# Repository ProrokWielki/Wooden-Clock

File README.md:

# PROJECT IN PROGRESS #

## How to build ##

### Pull the repo and all submodules ###

```
git clone --recurse-submodules https://github.com/ProrokWielki/Wooden-Clock.git
```

### Pull the docker image ###
```
docker pull pawelwarzecha/wooden_clock:0.5.2
```

### Run docker ###

```
docker run \
  --privileged \
  --network=host \
  -e DISPLAY=:0 \
  -e XAUTHORITY=/tmp/.Xauthority \
  -v $HOME/.Xauthority:/tmp/.Xauthority \
  -v /dev/bus/usb:/dev/bus/usb \
  -v /dev/:/dev/ \
  -v ./Wooden-Clock:/workspaces \
  -it pawelwarzecha/wooden_clock:0.5.2
```

### Build - inside docker ###

#### Supported build types ###
```
    ARM_Release  Release build - no debug symbols and 02
    ARM_Debug    Debug build - debug symbols and 00
    ARM_Size     Size optimized build - no debug symbols
    ARM_Speed    Speed optimized build - no debug symbols
    x86_Clang    Builds libs and unit tests for host machine using clang
    x86_GCC      Builds libs and unit tests for host machine using gcc
```
* **x86_*** builds are used for testing the project on the PC. CAn be used to run unit tests or use the GUI to emulate the hardware.
* **ARM_*** builds are for running the project on the dedicated board and running the `HIL` tests.

#### building ####

```
cd /workspaces/Software/STM
mkdir build
cd build
cmake -DCMAKE_BUILD_TYPE=<BUILD_TYPE> ..
make
```

## Running ##

### x86 build ###

#### Running unit tests ####

```
make test
```

#### Running the simulator ####

```
./src/pc/WoodenClockSimulator
```

### ARM build ###

For this you need to connect the board to the PC to be able to flash the software.

#### Running HIL tests ####

This will flash the target with the test bin and test if the behavior of the board is correct.

```
make test
```

#### Flashing the software ####

##### Flashing the internal flash ####

```
make flash
```

##### Flahsing the external flash ####

```
cd /workspaces/Software/Flasher
make
./flasher.py --file /workspaces/Software/STM/buil2/src/stm32/WoodenClock.elf --dev /dev/ttyUSB0
```

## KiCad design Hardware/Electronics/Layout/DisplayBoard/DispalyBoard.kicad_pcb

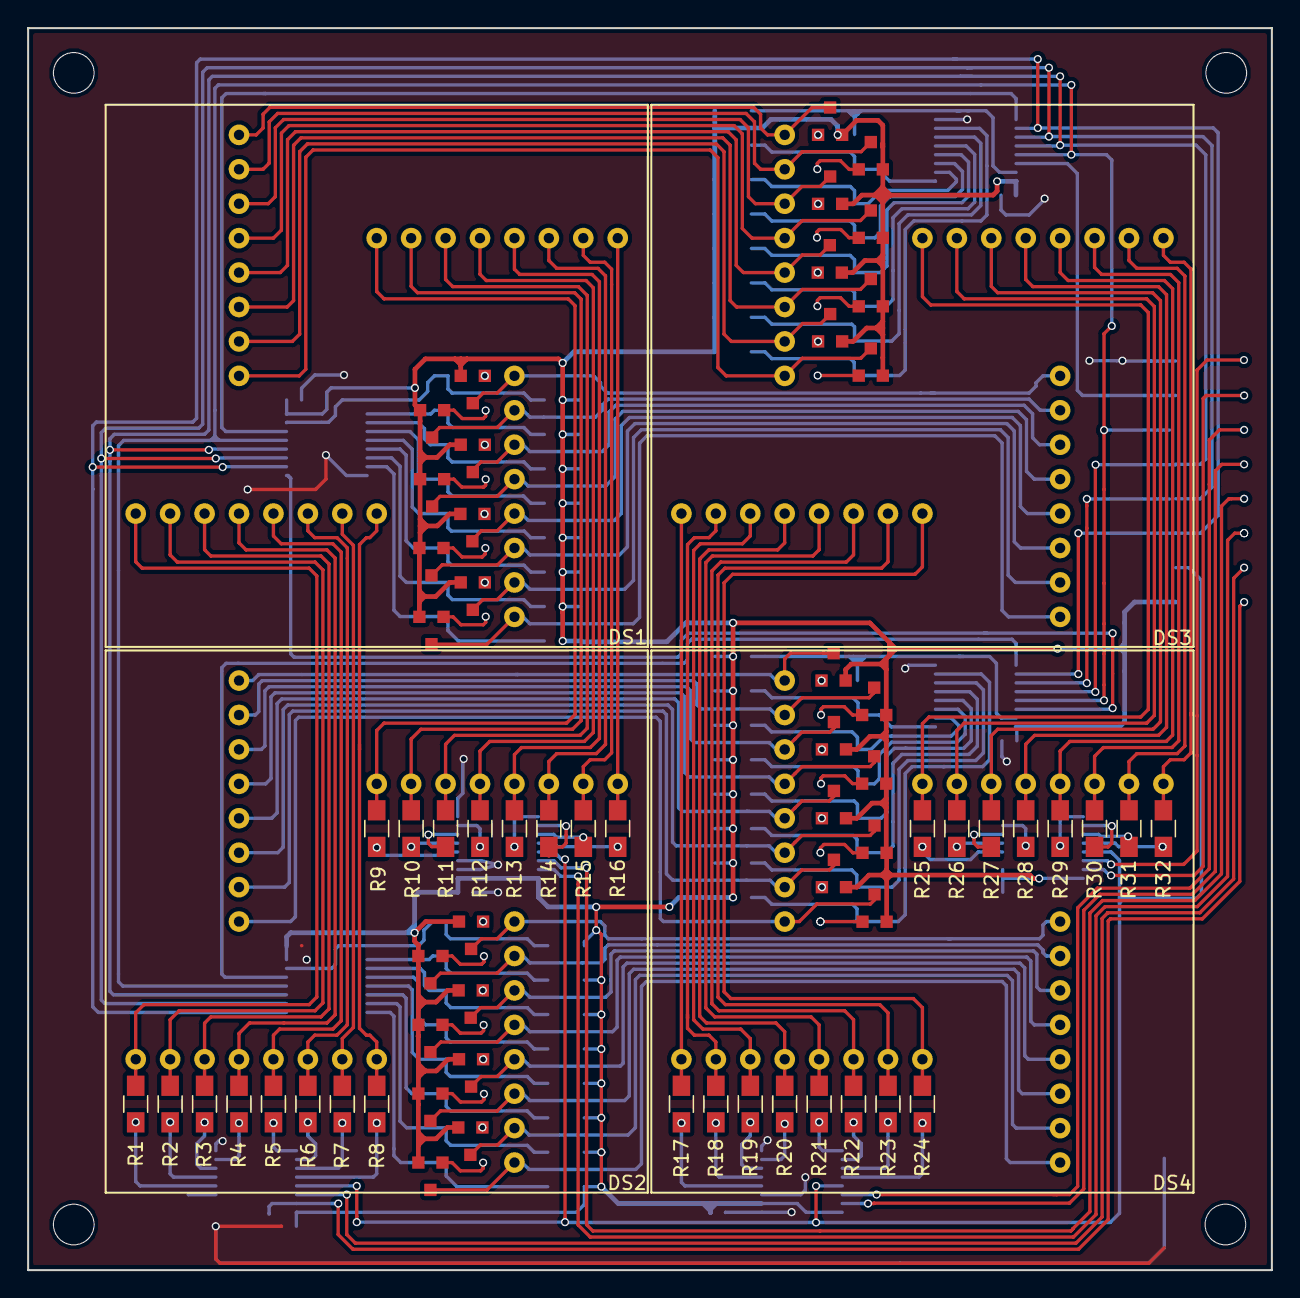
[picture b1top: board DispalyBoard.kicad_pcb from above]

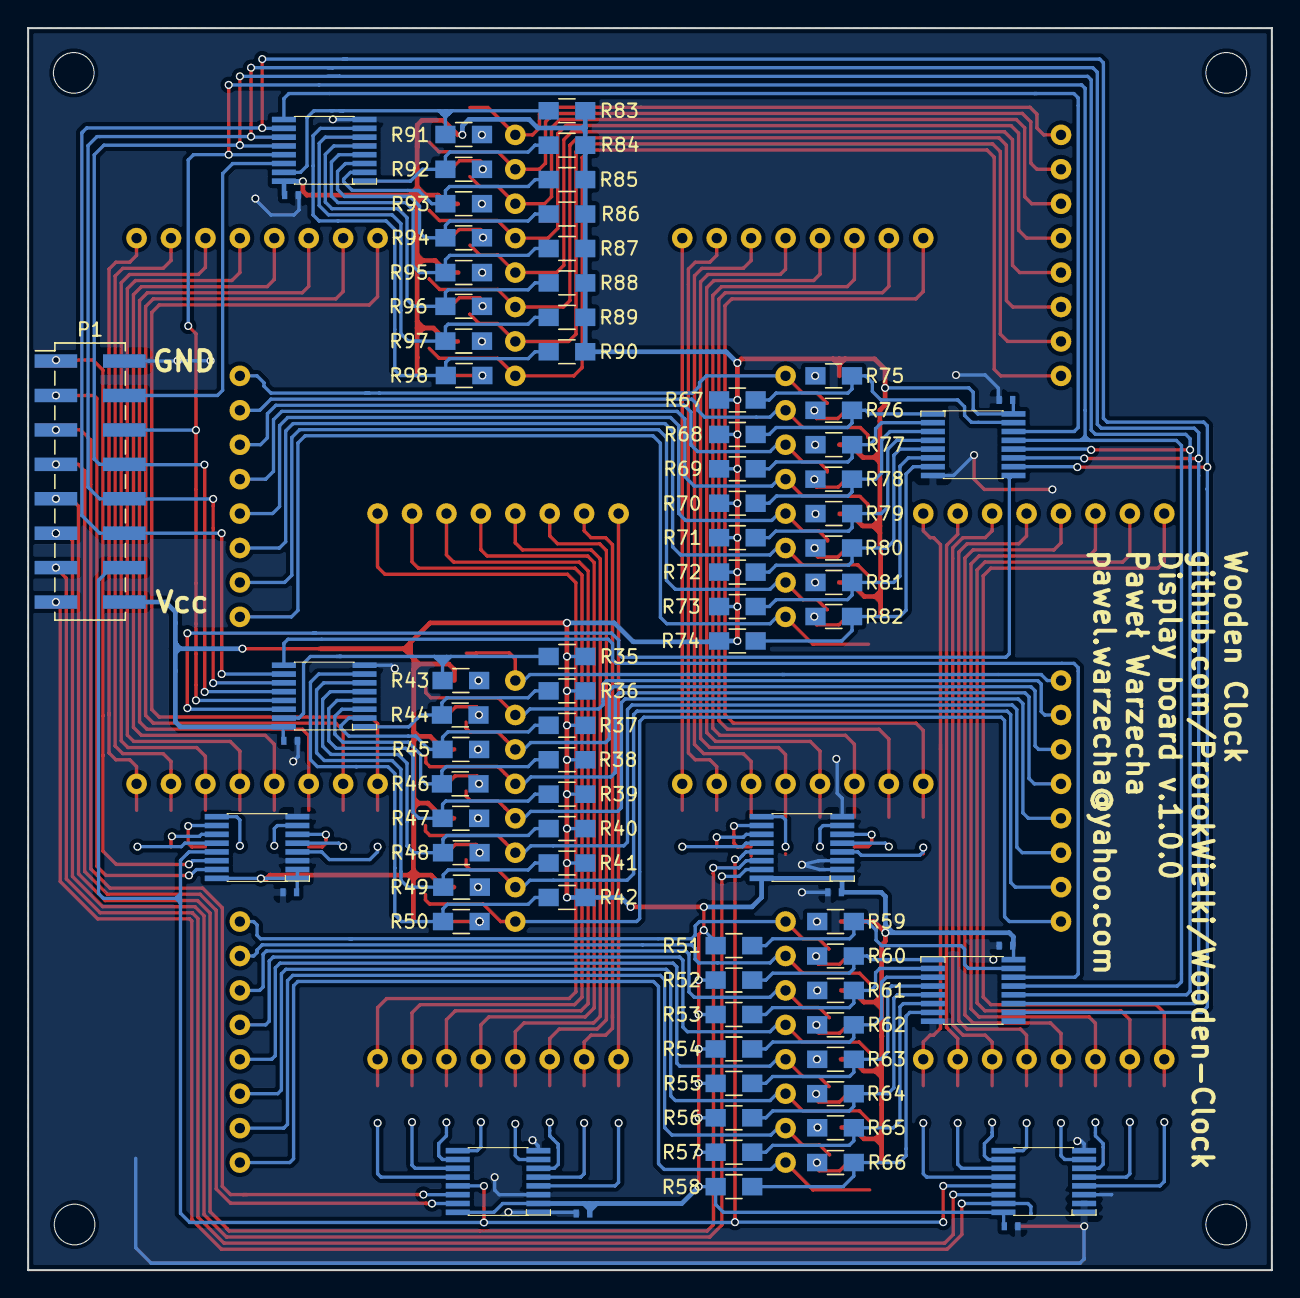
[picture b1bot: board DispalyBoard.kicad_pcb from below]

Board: 2 copper layers, 91.8 x 91.6 mm, 149 parts (81 on the bottom side), 179 nets.

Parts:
C1, C2, C3, C4, C5, C6, C7, C8: 100n; C0402
DS1, DS2, DS3, DS4: LM-1616015-CC; LM1616X15
P1: CONN_02X08; Pin_Header_Straight_2x08_Pitch2.54mm_SMD
Q1, Q2, Q3, Q4, Q5, Q6, Q7, Q8, Q9, Q10, Q11, Q12, Q13, Q14, Q15, Q16, Q17, Q18, Q19, Q20, Q21, Q22, Q23, Q24, Q25, Q26, Q27, Q28, Q29, Q30, Q31, Q32: TSM3401; SOT23-3
R1, R2, R3, R4, R5, R6, R7, R8, R9, R10, R11, R12, R13, R14, R15, R16, R17, R18, R19, R20, R21, R22, R23, R24, R25, R26, R27, R28, R29, R30, R31, R32: 47; R_0805_HandSoldering
R35, R36, R37, R38, R39, R40, R41, R42, R51, R52, R53, R54, R55, R56, R57, R58, R67, R68, R69, R70, R71, R72, R73, R74, R83, R84, R85, R86, R87, R88, R89, R90: 100k; R_0805_HandSoldering
R43, R44, R45, R46, R47, R48, R49, R50, R59, R60, R61, R62, R63, R64, R65, R66, R75, R76, R77, R78, R79, R80, R81, R82, R91, R92, R93, R94, R95, R96, R97, R98: 100; R_0805_HandSoldering
U1, U2, U3, U4: TLC59208F; TSSOP16
U5, U6, U7, U8: 74HC595; TSSOP16

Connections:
+3V3: C1.1, C2.1, C3.1, C4.1, C5.1, C6.1, C7.1, C8.1, P1.16, Q1.2, Q2.2, Q3.2, Q4.2, Q5.2, Q6.2, Q7.2, Q8.2, Q9.2, Q10.2, Q11.2, Q12.2, Q13.2, Q14.2, Q15.2, Q16.2, Q17.2, Q18.2, Q19.2, Q20.2, Q21.2, Q22.2, Q23.2, Q24.2, Q25.2, Q26.2, Q27.2, Q28.2, Q29.2, Q30.2, Q31.2, Q32.2, R35.1, R36.1, R37.1, R38.1, R39.1, R40.1, R41.1, R42.1, R51.1, R52.1, R53.1, R54.1, R55.1, R56.1, R57.1, R58.1, R67.1, R68.1, R69.1, R70.1, R71.1, R72.1, R73.1, R74.1, R83.1, R84.1, R85.1, R86.1, R87.1, R88.1, R89.1, R90.1, U1.16, U2.1, U2.16, U3.2, U3.16, U4.1, U4.2, U4.16, U5.16, U6.16, U7.16, U8.16
/C1: DS1.1, DS2.1, R1.2
/C2: DS1.2, DS2.2, R2.2
/C3: DS1.3, DS2.3, R3.2
/C4: DS1.4, DS2.4, R4.2
/C5: DS1.5, DS2.5, R5.2
/C6: DS1.6, DS2.6, R6.2
/C7: DS1.7, DS2.7, R7.2
/C8: DS1.8, DS2.8, R8.2
/C9: DS1.24, DS2.24, R9.2
/C10: DS1.23, DS2.23, R10.2
/C11: DS1.22, DS2.22, R11.2
/C12: DS1.21, DS2.21, R12.2
/C13: DS1.20, DS2.20, R13.2
/C14: DS1.19, DS2.19, R14.2
/C15: DS1.18, DS2.18, R15.2
/C16: DS1.17, DS2.17, R16.2
/C17: DS3.1, DS4.1, R17.2
/C18: DS3.2, DS4.2, R18.2
/C19: DS3.3, DS4.3, R19.2
/C20: DS3.4, DS4.4, R20.2
/C21: DS3.5, DS4.5, R21.2
/C22: DS3.6, DS4.6, R22.2
/C23: DS3.7, DS4.7, R23.2
/C24: DS3.8, DS4.8, R24.2
/C25: DS3.24, DS4.24, R25.2
/C26: DS3.23, DS4.23, R26.2
/C27: DS3.22, DS4.22, R27.2
/C28: DS3.21, DS4.21, R28.2
/C29: DS3.20, DS4.20, R29.2
/C30: DS3.19, DS4.19, R30.2
/C31: DS3.18, DS4.18, R31.2
/C32: DS3.17, DS4.17, R32.2
/CLK: P1.10, U5.11, U6.11, U7.11, U8.11
/LAT: P1.8, U5.12, U6.12, U7.12, U8.12
/MosfetMultiplexer9-16/SIN: U7.14, U8.9
/MosfetMultiplexer17-24/SIN: U5.14, U7.9
/MosfetMultiplexer25-32/SIN: U5.9, U6.14
/OE: P1.6, U5.13, U6.13, U7.13, U8.13
/R1: DS1.25, DS3.25, Q25.3
/R2: DS1.26, DS3.26, Q26.3
/R3: DS1.27, DS3.27, Q27.3
/R4: DS1.28, DS3.28, Q28.3
/R5: DS1.29, DS3.29, Q29.3
/R6: DS1.30, DS3.30, Q30.3
/R7: DS1.31, DS3.31, Q31.3
/R8: DS1.32, DS3.32, Q32.3
/R9: DS1.16, DS3.16, Q17.3
/R10: DS1.15, DS3.15, Q18.3
/R11: DS1.14, DS3.14, Q19.3
/R12: DS1.13, DS3.13, Q20.3
/R13: DS1.12, DS3.12, Q21.3
/R14: DS1.11, DS3.11, Q22.3
/R15: DS1.10, DS3.10, Q23.3
/R16: DS1.9, DS3.9, Q24.3
/R17: DS2.25, DS4.25, Q1.3
/R18: DS2.26, DS4.26, Q2.3
/R19: DS2.27, DS4.27, Q3.3
/R20: DS2.28, DS4.28, Q4.3
/R21: DS2.29, DS4.29, Q5.3
/R22: DS2.30, DS4.30, Q6.3
/R23: DS2.31, DS4.31, Q7.3
/R24: DS2.32, DS4.32, Q8.3
/R25: DS2.16, DS4.16, Q9.3
/R26: DS2.15, DS4.15, Q10.3
/R27: DS2.14, DS4.14, Q11.3
/R28: DS2.13, DS4.13, Q12.3
/R29: DS2.12, DS4.12, Q13.3
/R30: DS2.11, DS4.11, Q14.3
/R31: DS2.10, DS4.10, Q15.3
/R32: DS2.9, DS4.9, Q16.3
/RESET: P1.14, U1.13, U2.13, U3.13, U4.13
/RST: P1.12, U5.10, U6.10, U7.10, U8.10
/SCL1: P1.13, U1.14
/SCL2: P1.9, U2.14
/SCL3: P1.5, U3.14
/SCL4: P1.1, U4.14
/SDA1: P1.15, U1.15
/SDA2: P1.11, U2.15
/SDA3: P1.7, U3.15
/SDA4: P1.3, U4.15
/SIN: P1.4, U8.14
GND: C1.2, C2.2, C3.2, C4.2, C5.2, C6.2, C7.2, C8.2, P1.2, U1.1, U1.2, U1.3, U1.8, U2.2, U2.3, U2.8, U3.1, U3.3, U3.8, U4.3, U4.8, U5.8, U6.8, U7.8, U8.8
unnamed: Q1.1, R43.1
unnamed: Q2.1, R44.1
unnamed: Q3.1, R45.1
unnamed: Q4.1, R46.1
unnamed: Q5.1, R47.1
unnamed: Q6.1, R48.1
unnamed: Q7.1, R49.1
unnamed: Q8.1, R50.1
unnamed: Q9.1, R59.1
unnamed: Q10.1, R60.1
unnamed: Q11.1, R61.1
unnamed: Q12.1, R62.1
unnamed: Q13.1, R63.1
unnamed: Q14.1, R64.1
unnamed: Q15.1, R65.1
unnamed: Q16.1, R66.1
unnamed: Q17.1, R75.1
unnamed: Q18.1, R76.1
unnamed: Q19.1, R77.1
unnamed: Q20.1, R78.1
unnamed: Q21.1, R79.1
unnamed: Q22.1, R80.1
unnamed: Q23.1, R81.1
unnamed: Q24.1, R82.1
unnamed: Q25.1, R91.1
unnamed: Q26.1, R92.1
unnamed: Q27.1, R93.1
unnamed: Q28.1, R94.1
unnamed: Q29.1, R95.1
unnamed: Q30.1, R96.1
unnamed: Q31.1, R97.1
unnamed: Q32.1, R98.1
unnamed: R1.1, U1.4
unnamed: R2.1, U1.5
unnamed: R3.1, U1.6
unnamed: R4.1, U1.7
unnamed: R5.1, U1.9
unnamed: R6.1, U1.10
unnamed: R7.1, U1.11
unnamed: R8.1, U1.12
unnamed: R9.1, U2.4
unnamed: R10.1, U2.5
unnamed: R11.1, U2.6
unnamed: R12.1, U2.7
unnamed: R13.1, U2.9
unnamed: R14.1, U2.10
unnamed: R15.1, U2.11
unnamed: R16.1, U2.12
unnamed: R17.1, U3.4
unnamed: R18.1, U3.5
unnamed: R19.1, U3.6
unnamed: R20.1, U3.7
unnamed: R21.1, U3.9
unnamed: R22.1, U3.10
unnamed: R23.1, U3.11
unnamed: R24.1, U3.12
unnamed: R25.1, U4.4
unnamed: R26.1, U4.5
unnamed: R27.1, U4.6
unnamed: R28.1, U4.7
unnamed: R29.1, U4.9
unnamed: R30.1, U4.10
unnamed: R31.1, U4.11
unnamed: R32.1, U4.12
unnamed: R35.2, R43.2, U5.15
unnamed: R36.2, R44.2, U5.1
unnamed: R37.2, R45.2, U5.2
unnamed: R38.2, R46.2, U5.3
unnamed: R39.2, R47.2, U5.4
unnamed: R40.2, R48.2, U5.5
unnamed: R41.2, R49.2, U5.6
unnamed: R42.2, R50.2, U5.7
unnamed: R51.2, R59.2, U6.15
unnamed: R52.2, R60.2, U6.1
unnamed: R53.2, R61.2, U6.2
unnamed: R54.2, R62.2, U6.3
unnamed: R55.2, R63.2, U6.4
unnamed: R56.2, R64.2, U6.5
unnamed: R57.2, R65.2, U6.6
unnamed: R58.2, R66.2, U6.7
unnamed: R67.2, R75.2, U7.15
unnamed: R68.2, R76.2, U7.1
unnamed: R69.2, R77.2, U7.2
unnamed: R70.2, R78.2, U7.3
unnamed: R71.2, R79.2, U7.4
unnamed: R72.2, R80.2, U7.5
unnamed: R73.2, R81.2, U7.6
unnamed: R74.2, R82.2, U7.7
unnamed: R83.2, R91.2, U8.15
unnamed: R84.2, R92.2, U8.1
unnamed: R85.2, R93.2, U8.2
unnamed: R86.2, R94.2, U8.3
unnamed: R87.2, R95.2, U8.4
unnamed: R88.2, R96.2, U8.5
unnamed: R89.2, R97.2, U8.6
unnamed: R90.2, R98.2, U8.7

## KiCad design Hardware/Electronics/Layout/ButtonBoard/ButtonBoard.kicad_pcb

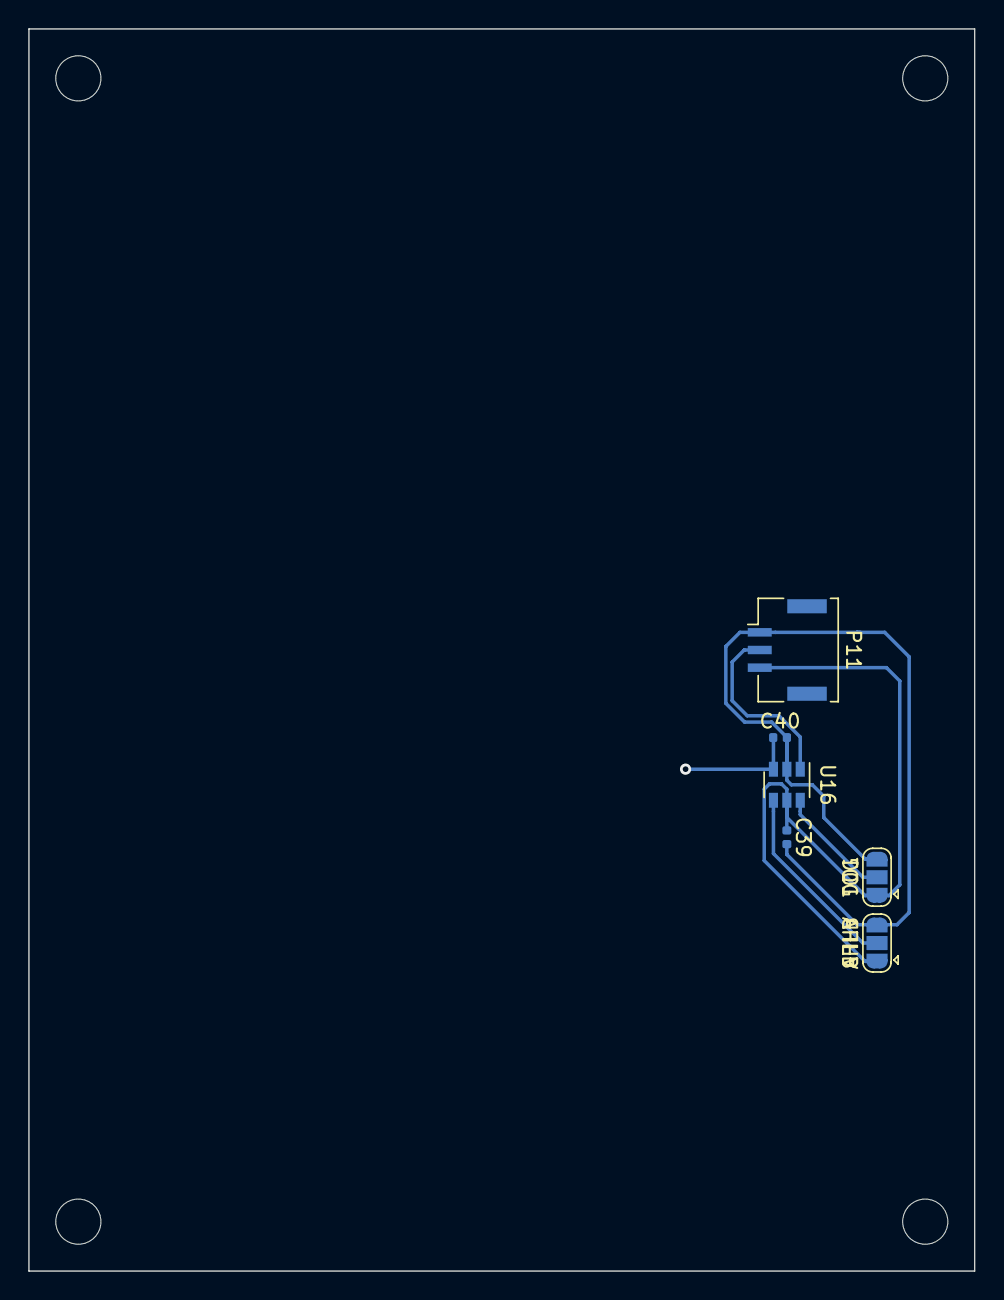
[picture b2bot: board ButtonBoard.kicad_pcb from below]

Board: 2 copper layers, 67.0 x 88.0 mm, 6 parts (6 on the bottom side), 6 nets.

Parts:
AHLB: AHLB; SolderJumper-3_P1.3mm_Open_RoundedPad1.0x1.5mm
C39: 1u; C_0402_1005Metric
C40: <50p; C_0402_1005Metric
P11: CONN_01X03; Molex_CLIK-Mate_502382-0370_1x03-1MP_P1.25mm_Vertical
TOG: TOG; SolderJumper-3_P1.3mm_Open_RoundedPad1.0x1.5mm
U16: TTP223; SOT-23-6

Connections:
+3V3: AHLB.1, C39.1, P11.3, TOG.1, U16.5
GND: AHLB.3, C39.2, C40.2, P11.1, TOG.3, U16.2
unnamed: AHLB.2, U16.4
unnamed: TOG.2, U16.6
OUTPUT: P11.2, U16.1
PAD: C40.1, U16.3

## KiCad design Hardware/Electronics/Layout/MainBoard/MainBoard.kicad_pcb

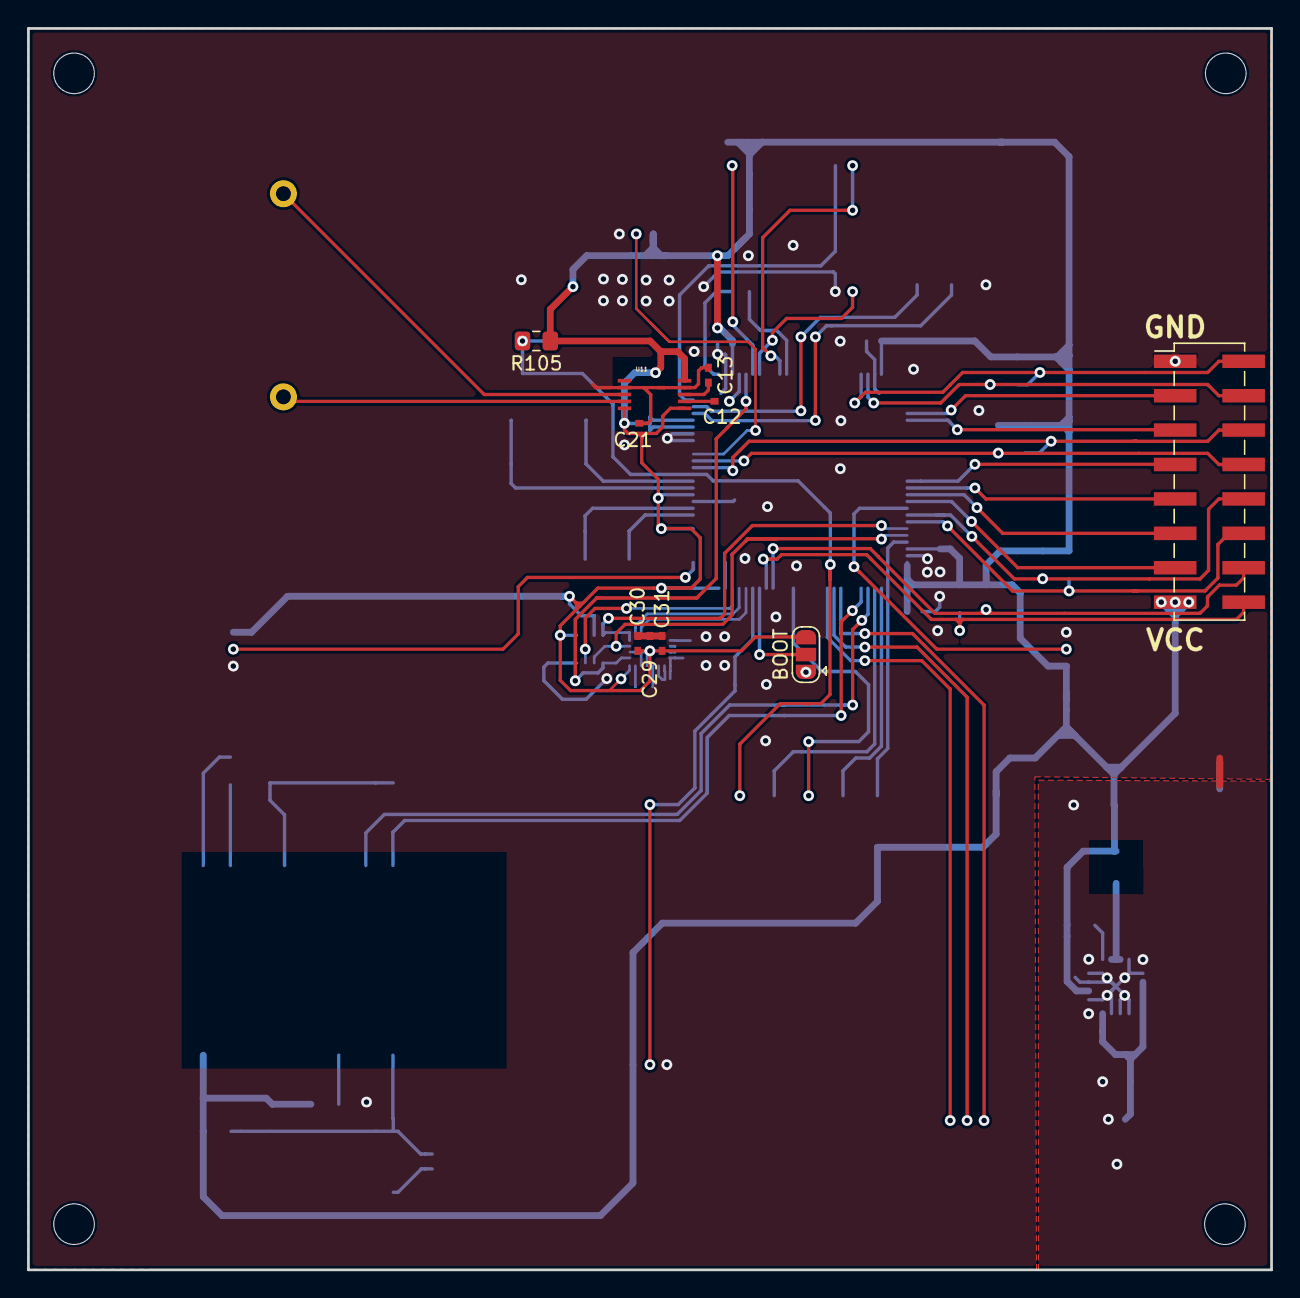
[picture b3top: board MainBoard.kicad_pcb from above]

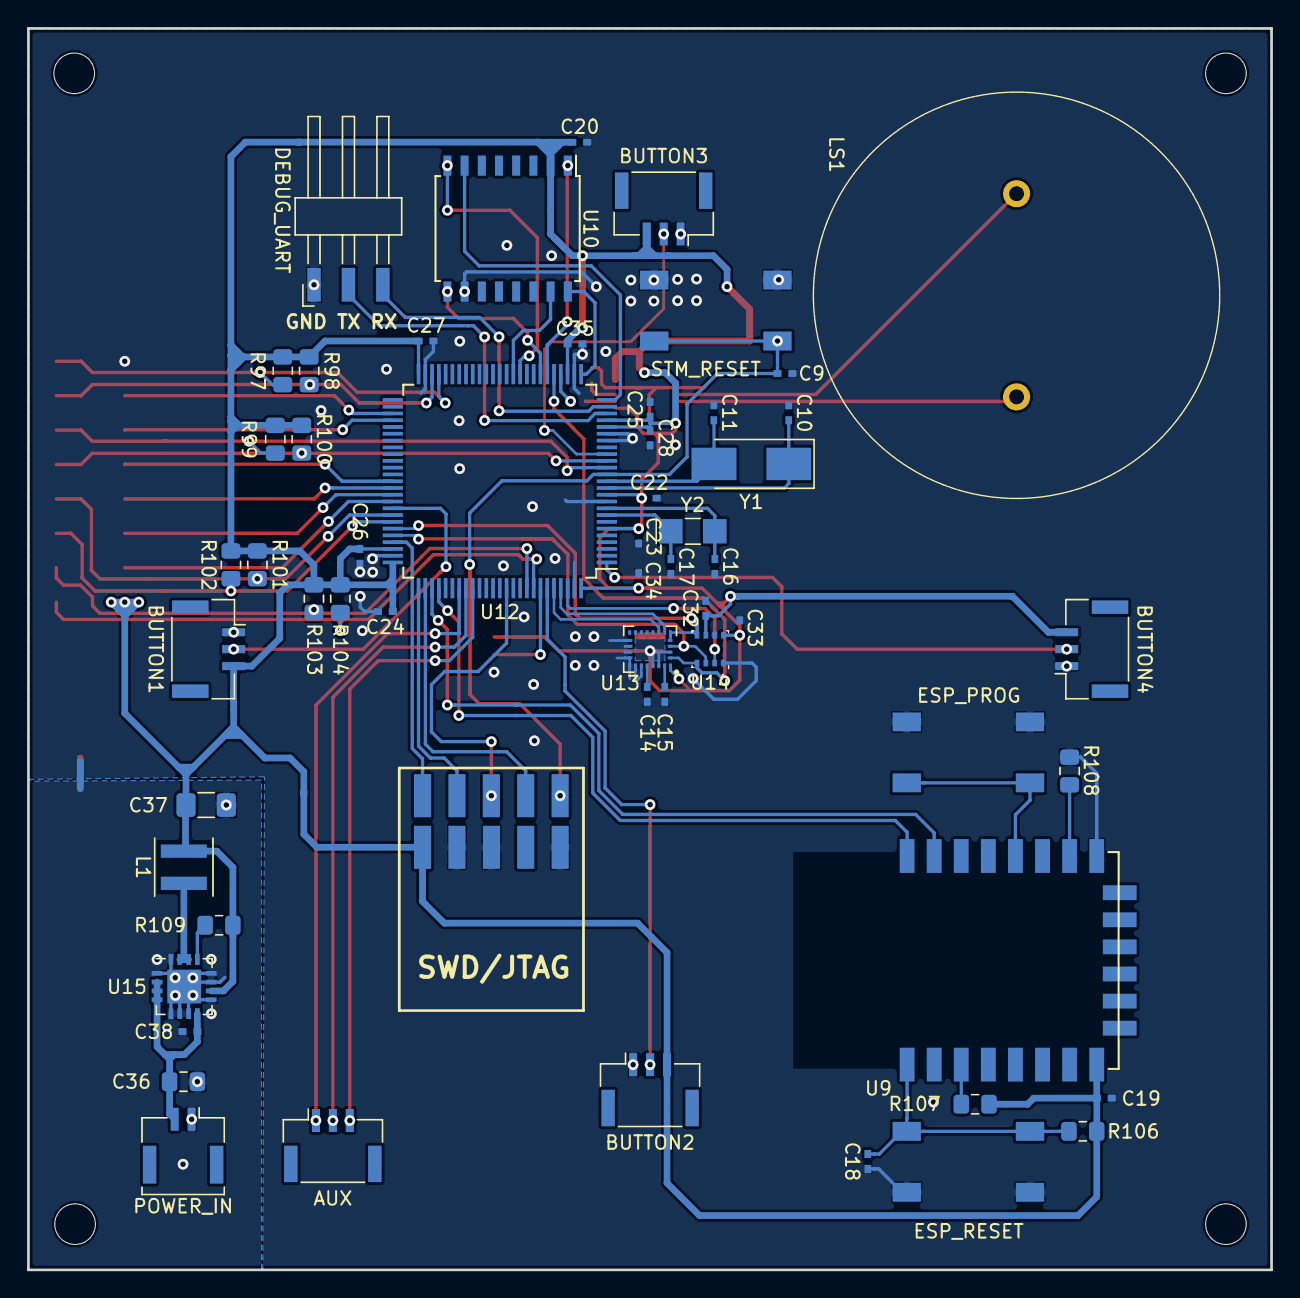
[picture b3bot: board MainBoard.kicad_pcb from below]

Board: 2 copper layers, 91.8 x 91.6 mm, 67 parts (57 on the bottom side), 63 nets.

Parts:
C9, C15, C18, C19, C20, C22, C23, C24, C25, C26, C27, C28, C30, C31, C32, C33, C34, C35: 100n; C_0402_NoSilk
C10, C11: 7.5p; C_0402_NoSilk
C12, C13, C21, C38: 1u; C_0402_NoSilk
C14: 10n; C_0402_NoSilk
C16, C17: 4pF; C_0402_NoSilk
C29: 10u; C_0402_NoSilk
C36: 10u; C_0805_2012Metric_Pad1.15x1.40mm_HandSolder
C37: 22u; C_1206_3216Metric_Pad1.42x1.75mm_HandSolder
JP1: BOOT; SolderJumper-3_P1.3mm_Open_RoundedPad1.0x1.5mm
L1: 6u8; L_Coilcraft_XxL4040
LS1: BDT3016H12
P2: CONN_02X08; Pin_Header_Straight_2x08_Pitch2.54mm_SMD
P3: SWD/JTAG; SAMTEC-TSM-105-01-X-DH
P4: BUTTON1; Molex_CLIK-Mate_502386-0370_1x03-1MP_P1.25mm_Horizontal
P5: BUTTON2; Molex_CLIK-Mate_502386-0370_1x03-1MP_P1.25mm_Horizontal
P6: BUTTON3; Molex_CLIK-Mate_502386-0370_1x03-1MP_P1.25mm_Horizontal
P7: BUTTON4; Molex_CLIK-Mate_502386-0370_1x03-1MP_P1.25mm_Horizontal
P8: POWER_IN; Molex_CLIK-Mate_502382-0270_1x02-1MP_P1.25mm_Vertical
P9: DEBUG_UART; Harwin_M20-89003xx_1x03_P2.54mm_Horizontal
P10: AUX; Molex_CLIK-Mate_502386-0370_1x03-1MP_P1.25mm_Horizontal
R97, R98, R99, R100, R101, R102, R103, R104, R105, R106, R107, R108: 4k7; R_0805_2012Metric_Pad1.15x1.40mm_HandSolder
R109: 1M; C_0805_2012Metric_Pad1.15x1.40mm_HandSolder
SW1: STM_RESET; E-switch_6x6mm
SW2: ESP_RESET; E-switch_6x6mm
SW3: ESP_PROG; E-switch_6x6mm
U9: ESP-12F; ESP-12E_SMD
U10: S25FL129P; SOIC-16W_7.5x10.3mm_P1.27mm
U11: MAX9700; MSOP10-0.5
U12: STM32L452VCTx; LQFP-100_14x14mm_P0.5mm
U13: LSM9DS1; LGA-24L_3x3.5mm_P0.43mm
U14: BME280; Bosch_LGA-8_2.5x2.5mm_P0.65mm_ClockwisePinNumbering
U15: TPS6211; QFN-16-1EP_4x4mm_P0.65mm_EP2.5x2.5mm
Y1: 8MHz; Crystal_SMD_Abracon_ABM3-2Pin_5.0x3.2mm_HandSoldering
Y2: 32.768kHz; Crystal_SMD_MicroCrystal_CC7V-T1A-2Pin_3.2x1.5mm_HandSolder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

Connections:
+3V3: C19.1, C20.2, C21.2, C22.2, C23.2, C24.2, C25.2, C26.2, C27.2, C28.2, C29.2, C30.2, C31.2, C32.2, C33.2, C34.2, C35.2, C37.1, JP1.3, L1.2, P2.15, P3.1, P4.3, P5.3, P6.3, P7.3, R97.1, R98.1, R99.1, R100.1, R101.1, R102.1, R103.1, R104.1, R105.1, R106.1, R107.1, R109.1, U9.8, U10.2, U11.1, U11.5, U11.10, U12.6, U12.11, U12.21, U12.22, U12.28, U12.50, U12.73, U12.75, U12.100, U13.1, U13.3, U13.22, U13.23, U14.6, U14.8, U15.10
/DisplayBoard/DATA_IN: P2.3, U12.53
/DisplayBoard/LATCH: P2.7, U12.63
/DisplayBoard/SCL1: P2.10, R101.2, U12.68
/DisplayBoard/SCL2: P2.2, R97.2, U12.47
/DisplayBoard/SCL3: P2.6, R99.2, U12.15
/DisplayBoard/SCL4: P2.14, R103.2, U12.92
/DisplayBoard/SDA1: P2.12, R102.2, U12.69
/DisplayBoard/SDA2: P2.4, R98.2, U12.48
/DisplayBoard/SDA3: P2.8, R100.2, U12.16
/DisplayBoard/SDA4: P2.16, R104.2, U12.93
/MainBoard/CLOCK: P2.9, U12.64
/MainBoard/CS: U10.7, U12.25
/MainBoard/IO0: U10.15, U12.36
/MainBoard/IO1: U10.8, U12.35
/MainBoard/IO2: U10.9, U12.32
/MainBoard/IO3: U10.1, U12.31
/MainBoard/OE: P2.5, U12.54
/MainBoard/RESET: P2.11, U12.65
/MainBoard/RST: P2.13, U12.66
/MainBoard/SCK: U10.16, U12.26
/MainBoard/SPI1_CS1: U12.97, U13.7
/MainBoard/SPI1_CS2: U12.96, U13.8
/MainBoard/SPI1_CS3: U12.98, U14.2
/MainBoard/SPI1_MISO: U12.70, U13.5, U13.6, U14.5
/MainBoard/SPI1_MOSI: U12.71, U13.4, U14.3
/MainBoard/SPI1_SCK: U12.30, U13.2, U14.4
/MainBoard/TCK: P3.4, U12.76
/MainBoard/TDI: P3.8, U12.77
/MainBoard/TDO: P3.6, U12.89
/MainBoard/TMS: P3.2, U12.72
AUX_1: P10.1, U12.82
AUX_2: P10.2, U12.83
AUX_3: P10.3, U12.84
BUTTON1: P4.2, U12.67
BUTTON2: P5.2, U12.95
BUTTON3: P6.2, U12.17
BUTTON4: P7.2, U12.1
ESP_RX: U9.15, U12.78
ESP_TX: U9.16, U12.79
GND: C9.2, C10.2, C11.2, C13.1, C14.2, C15.2, C16.1, C17.1, C18.2, C19.2, C20.1, C21.1, C22.1, C23.1, C24.1, C25.1, C26.1, C27.1, C28.1, C29.1, C30.1, C31.1, C32.1, C33.1, C34.1, C35.1, C36.2, C37.2, C38.2, JP1.1, P2.1, P3.3, P3.5, P3.9, P4.1, P5.1, P6.1, P7.1, P8.1, P9.1, R108.2, SW1.1, SW2.1, SW3.2, U9.9, U10.10, U11.4, U11.7, U12.10, U12.19, U12.20, U12.27, U12.49, U12.74, U12.99, U13.14, U13.15, U13.16, U13.17, U13.18, U13.19, U13.20, U14.1, U14.7, U15.1, U15.5, U15.6, U15.7, U15.9, U15.11, U15.12, U15.16, U15.17
NRST: C9.1, P3.10, R105.2, SW1.2, U12.14
unnamed: C10.1, U12.12, Y1.1
unnamed: C11.1, U12.13, Y1.2
unnamed: C12.1, U11.2
unnamed: C12.2, U12.29
unnamed: C13.2, U11.3
unnamed: C14.1, U13.21
unnamed: C15.1, U13.24
unnamed: C16.2, U12.9, Y2.2
unnamed: C17.2, U12.8, Y2.1
unnamed: C18.1, R106.2, SW2.2, U9.1
unnamed: C36.1, C38.1, P8.2, U15.2, U15.3, U15.4, U15.8
unnamed: JP1.2, U12.94
unnamed: L1.1, U15.14, U15.15
unnamed: LS1.1, U11.8
unnamed: LS1.2, U11.9
unnamed: P9.2, U12.23
unnamed: P9.3, U12.24
unnamed: R107.2, U9.3
unnamed: R108.1, U9.10
unnamed: R109.2, U15.13
unnamed: SW3.1, U9.12

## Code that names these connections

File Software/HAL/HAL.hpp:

/**
 *  @file HAL.hpp
 *
 *  Created on: 21-11-2018
 *  @author: Paweł Warzecha
 */

#ifndef HAL_HAL_HPP_
#define HAL_HAL_HPP_

#include "Clock/Clock.hpp"
#include "DMA/DMA.hpp"
#include "GPIO/GPIO.hpp"
#include "I2C/I2C.hpp"
#include "SPI/SPI.hpp"
#include "Timer/Timer.hpp"

#include "74HC595/74HC595.hpp"
#include "BME280/BME280.hpp"
#include "LSM9DS1/LSM9DS1.hpp"
#include "TLC59208F/TLC59208F.hpp"

class LSM9DS1;

class HAL
{
public:
    static GPIO I2C1_SCL;
    static GPIO I2C1_SDA;

    static GPIO I2C2_SCL;
    static GPIO I2C2_SDA;

    static GPIO I2C3_SCL;
    static GPIO I2C3_SDA;

    static GPIO I2C4_SCL;
    static GPIO I2C4_SDA;

    static GPIO SPI1_MISO;
    static GPIO SPI1_MOSI;
    static GPIO SPI1_SCK;
    static GPIO SPI1_CS1;
    static GPIO SPI1_CS2;
    static GPIO SPI1_CS3;

    static GPIO QSPI_IO0;
    static GPIO QSPI_IO1;
    static GPIO QSPI_IO2;
    static GPIO QSPI_IO3;
    static GPIO QSPI_CLK;
    static GPIO QSPI_CS;

    static GPIO UART3_TX;
    static GPIO UART3_RX;

    static GPIO UART4_TX;
    static GPIO UART4_RX;

    static GPIO TLC_RESET;

    static GPIO SR_DATAIN;
    static GPIO SR_RCLOCK;
    static GPIO SR_SCLOCK;
    static GPIO SR_OE;
    static GPIO SR_CLEAR;

    static GPIO BUTTON1;
    static GPIO BUTTON2;
    static GPIO BUTTON3;
    static GPIO BUTTON4;

    static DMA DMA1_2;
    static DMA DMA1_4;
    static DMA DMA2_2;
    static DMA DMA2_7;
    static DMA DMA2_4;

    static I2C I2C_1;
    static I2C I2C_2;
    static I2C I2C_3;
    static I2C I2C_4;

    static SPI SPI_1;

    static SR_74HC595 SR_74HC595_1;

    static TLC59208F TLC59208F_1;
    static TLC59208F TLC59208F_2;
    static TLC59208F TLC59208F_3;
    static TLC59208F TLC59208F_4;

    static LSM9DS1 LSM9DS1_1;

    static BME280 BME280_1;

    static Timer Timer2;

    static void clock_init(void);
    static void QSPI_init(void);
    static void I2C_init(void);
    static void SPI_init(void);
    static void GPIO_Init(void);
    static void DMA_init();
    static void Timer_init();
    static void NVIC_init(void);
    static void TLC59208F_init(void);
    static void SR_74HC595_init(void);
    static void LSM9DS1_init();

    static void init(void);

    static bool up;
    static bool down;
    static bool left;
    static bool right;

private:
    HAL() = delete;
};
#endif /* HAL_HAL_HPP_ */

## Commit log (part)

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2018-08-19 Init Commit
2018-08-21 Moved schematics and laeyot to Hardware/Electronics
2018-08-21 deleted moved files
2018-08-21 Added files for the enclouser design
2018-08-21 Added software folder, with FreeRTOS
2018-10-21 Added combined model of the housing
2018-10-21 Changed dispaly board schematic and layout version to 1.0.0 Moved vias from the capacitor pads Added github link on the silkscreen Changed files architecture Pushed new gerbers
2018-11-18 Hal wrapper for the registers
2018-11-18 updated eclipse configuration
2018-11-18 added CMSIS for stm32l452
2018-11-18 Added wrpper for GPIO
2018-11-18 deleted empty file -- GPIO.cpp
2019-01-13 Added py_buildsystem configuration files
2019-01-13 Added doxygen configuration file
2019-01-13 Added Register template class
2019-01-13 added statrtup file systeminit file and linker script
2019-01-13 excluded outputdirectories from repo
2019-01-13 Added doxygen documentation
2019-01-13 Update of the GPIO class
2019-01-13 Added wrapper template class for the I2C
2019-01-17 Added method for setting the I2C timming
2019-01-17 using set_timing method for the I2Cs
2019-01-17 Updated the py_buildsystem configuration
2019-01-19 change all io opperations to HAL fnctions
2019-02-15 Added DMA,Dsiplay and Clock drafts, added HALL files
2019-02-24 Added draft of display class
2019-02-24 Added HAL modules
2019-02-24 updated Dispaly HAL module, main.cpp and py_puildsystem config
2019-02-24 updated HAL.cpp/hpp file
2019-02-24 Added missing assets
2019-02-24 updated main and assets
2019-02-24 fixed liner skript flag
2019-02-26 Added clang format config file
2019-02-26 added HAL DMA module
2019-02-28 Added drivers for TLC59208F and 74HC595
2019-02-28 clang format config update
2019-02-28 I2C can use DMA, using newly added drivers
2019-02-28 Added handling ISR
2019-03-02 Changed compiler to g++, added compilation flags
2019-03-02 Update of the eclipse configuration
2019-03-02 Added new test images
2019-03-02 removed old py_buildsystem config file
2019-03-02 using new DMA interrupt callback function
2019-03-02 Update of the display bsp module, first working
2019-03-02 Added settings multiple regiseters at once
2019-03-02 Adding interrupt callback possible
2019-03-02 doxygen comment update
2019-03-02 Changed DMA channels
2019-03-02 using display class
2019-03-02 Formating
2019-03-03 FreeRTOS update
2019-03-03 Added FreeRTOS tasks
2019-03-03 cleanup
2019-03-03 Added seprete config for building FreeRTOS
2019-03-03 using freertos handlers
2019-03-03 Added new function - seting all outputs to selected value
2019-03-03 Assigment off callback possible
2019-03-03 Small updates, mainly formating
2019-03-03 Moved initailization of display from main to dispaly class
2019-03-09 New images
2019-03-09 HAL refactoring
2019-03-09 drivers refactor
2019-03-09 BSP refactoring
2019-03-09 Freertos config update
2019-03-09 Formating and more heap and stacj
2019-03-09 ISR handling update
2019-03-09 eclipse configuration update
2019-03-12 Added Button class
2019-03-12 Added DataContainer
2019-03-12 compiling with fast optimization, assets compiled with APP
2019-03-12 removed irq enabling/disabling
2019-03-12 Added buttons to bsp
2019-03-12 updating buttons in task
2019-03-12 Added State machines and 3 states
2019-05-05 LSM9DS1 driver implementation
2019-05-05 SPI wrapper
2019-05-05 Added new states
2019-05-05 StateMachine update
2019-05-05 py_buildsyste update
2019-05-05 Schematic update -- start of the main board designe
2019-05-05 minor changes
2019-06-08 disabled specs=nano.specs -- it disebles exception handling
2019-06-08 Draft of the magnetometer class
2019-09-21 added submodule EmbedGUI
2019-09-21 eclipse config update
2019-09-21 Updated EmbedGUI
2019-09-21 Added Text2CArray config
2019-09-21 Updated py_buildsystem config - building EmbedGUI
2020-05-03 Changed pullup resistors on the gates of mosfets to 4k7 - faster gate discharge
2020-05-03 Added main board design
2020-05-03 Added button board design
2020-05-03 added texts
2020-05-03 added methods for checking WHO_AM_I registers, turned on gyro on init
2020-05-03 added methods for cashing led vealues before sending them
2020-05-03 BME280 drivers
2020-05-03 added placeholder for USART
2020-05-03 added simple ESP program - allows for clock controlling through mqtt
2020-05-03 added gitignore
2020-05-03 added screens
2020-05-03 addedmethod to add half transfer interrupt callback
2020-05-03 fix stop_transfer
2020-05-03 Addapted to the PCB design, QSPI test, reciving data from ESP
2020-05-03 line drawing updated
2020-05-03 Accelerometer place holder
2020-05-03 Gyroscope place holder
2020-05-03 external flash config - commented
2020-05-03 possible to conter with ESP, dipslay task called more frequently
2020-05-20 set value of the capacitor on the button board, changed resitor value on the display board
2020-05-20 new screen to test buttons, touch buttons handling
2020-05-20 new version of EmbedGUI
2021-01-31 new arrows
2021-01-31 py_buildsystem config update
2021-01-31 new arrows added to StateButtun
2021-02-01 added readme
2021-02-01 fixed buttons
2021-02-02 Correct buttons names
2021-04-18 changed directories structure
2021-04-18 moved ESP to Software/ESP
2021-04-18 added records to gitignore
2021-04-18 draft of the flasher
2024-12-23 added clang-format config file
2024-12-23 renamed clang-format file
2025-03-03 added CMSIS and FreeRTOS as submodules
2025-03-03 updated to files from newest CMSIS
2025-03-09 added .gitignore for STM
2025-03-16 remved eclipse config
2025-03-16 added build to .gitignore
2025-03-16 added clang-tidy config file
2025-03-16 added cofig for cmake-format
2025-03-16 moved libs
2025-03-16 removed EmbedGUI
2025-03-16 added EmbedGUI as submodule
2025-06-03 removed py_buildsystem
2025-06-03 moved stm code to stm dir
2025-06-03 moved APP to src/APP
2025-06-03 added tests
2025-06-03 added devcontainer
2025-06-03 updated gitmodules
2025-06-03 added CMake stuff
2025-07-20 added text2CArray as submodule
2025-07-20 added new texts and font
2025-07-20 updated submodules
2025-07-20 updated devcontainer
2025-07-20 created seperate build for stm and pc
2025-07-20 trying to run github acions
2025-07-20 moved github actions to correct place
2025-07-20 fixed github actions typo
2025-07-20 used correct image
2025-07-20 used correct image version
2025-07-20 added actual build steps
2025-07-20 added more builds
2025-07-20 pulling submodules
2025-07-20 disabled dummy test
2025-07-20 fixed submodule pull
2025-07-20 fixed x86 build
2025-07-27 refactored os_abstraction
2025-07-27 added thermometer
2025-07-27 refactored assets to fit new EmbedGui
2025-07-27 refactored pc part
2025-07-27 added 'dot' to texts
2025-07-27 added venv dir to gitignore
2025-07-27 updated schematics
2025-10-04 Refactored Assets
2025-10-04 BSP is now Singleton
2025-10-04 DataContainer is now Singleton
2025-10-04 Refactored os_abstarcion
2025-10-04 Fixed typos and clang findings
2025-10-05 RTC clock operational from Clock class
2025-10-05 Added ISR register to RTC
2025-10-05 fixed RTC bug
2025-10-10 copy compile_commands.json to root
2025-10-18 Extended USART class
    Now it can handle rx not empty and idle interrupts
2025-10-18 Communication class
    Simple class for handling messages
2025-10-18 fixed typos
2025-10-18 DMA requests setup handling
2025-10-18 Platform handling in the main CMakeLists.txt
    Moved handling for which platfomr the software is build to
    the main CMakeLists.txt - this makes compile_commands.json
    to only contatin sources relevant for the given build
2025-10-18 fixed typo
2025-10-18 HAL is now singleton and using communication class
2025-10-18 helper script for clang-tidy
2025-10-18 removed rule from being enforced by clang-tidy
2025-10-19 removed cmsis header form i2c class
2025-10-19 Added minimal power class
2025-10-19 bug fix in communication
2025-10-19 extended clock class
2025-10-19 remvoed cmsis from rtc
2025-10-19 PC build working again
2025-10-19 uncommented gpio test
2025-10-19 submodule with bmew70 api
2025-10-19 "integrated" bme280 api
2025-10-19 using bme lib
2025-12-02 Kicad files cleanup
2025-12-03 enforce some styling rules
2025-12-03 Added sytem config wrapper
2025-12-03 use of system config
2025-12-03 formatting
2025-12-03 improved coverage report generation
2025-12-03 use of new embedgui
2025-12-03 OS Cmake cleanup
2025-12-03 using spans and std::arrys
2025-12-03 general improvements
2026-05-09 Flash class
2026-05-09 Extend Clock class
2026-05-09 flash types
2026-05-09 clock types
2026-05-09 flash cmsis_bridge
2026-05-09 Clock cmsis_bridge
2026-05-09 cleanup hal from cmsis
2026-05-09 Cmakes cleanup
2026-05-09 fix some more clang-tidy findings
2026-05-10 added nanopb
2026-05-10 New docker image version
2026-05-10 proto message firts integration
2026-05-10 github workflow use new docker
2026-05-10 moved devcontainer dir to root
2026-05-11 Added arduino stuff to docker image
2026-05-11 build step for esp
2026-05-11 testing var for image version
2026-05-11 fixed arduino build step
2026-05-11 yet another try
2026-05-11 lets see
2026-05-11 shouldnt be needed ... but lets see
2026-05-11 added pubsubclient lib ... it should already be in the docker image
2026-05-12 Switched to platformio
2026-05-12 update actions
2026-05-13 Moved protos to common folder for ESP and STM
2026-05-14 Added clearing all USART interrupts so the program isnt getting stuck
2026-05-14 renamed message
2026-05-14 sending and reciving real time
2026-05-14 added network option so ESP can be flashe from devcontainer
2026-05-14 alligned PC BSP
2026-05-25 Adapt to new embedgui
2026-05-26 add method to write and read given data type from register
2026-05-26 Add method for sending data over UART
2026-05-26 Draft QSPI
2026-05-26 add draft bootloader
2026-05-26 add dummy bootloader for PC
2026-05-26 Integrate bootloader
2026-05-26 LSM9DS1 some refactoring
2026-05-26 Handling UART4 interrupt
2026-05-26 Added S25FL129 driver draft
2026-05-28 new sections
2026-05-28 use QSPI and S25FL129P
2026-05-28 extended communication interface
2026-05-28 integrate USART4 with communcition interface
2026-05-28 DebugMessageHandler
2026-05-28 Integrate DebugMessageHandler
2026-05-28 add "elf" to file name
2026-05-28 set C standard to 23
